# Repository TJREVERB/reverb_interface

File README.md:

# TJREVERB Interface Boards
Interface board rework, moved from Eagle to Kicad

The board provides power connections from the EPS and data connections from the flight computer to various components.

APRS and Iridium (through a MAX3232) are connected to UART, and can be selected between hardware UART and software/converter UART using jumpers. software/converter UART uses a converter as the primary UART device, with an option for software bit banging using RPi GPIO as a backup.

There are three branches: USB to UART, SPI to UART (DEPRECATED IN v1.4), and Multicore

The first is similar to the original design, and uses a USB to UART converter. 

The second uses an SPI to UART converter so that we can send data through the main Pi header instead of pogo pins or USB pads. DEPRECATED DUE TO DIFFICULTY IN SOFTWARE IMPLEMENTATION

The third uses an external AVR microcontroller as a secondary core, to be used for IO operations, specifically as an SPI/I2C to UART converter and an I2C buffer for sending delayed commands to the EPS (e.g. sending bus reset after a delay to give the pi enough time to exit script)

All branches include connections to bitbang uart instead of using the converter.

## Versions
v1.0 initial

v1.1 routing improvements

v1.2 fabricated first, received 10/24/21

v1.3 adds major corrections for circuitry

v1.4 introduces the new multicore branch

v1.5 replaces LSM9DS1 IMU with BNO055

v1.6 adds RTC and battery

v2.0 CAD compatibility check, fabbed as v2 on 11/28/21

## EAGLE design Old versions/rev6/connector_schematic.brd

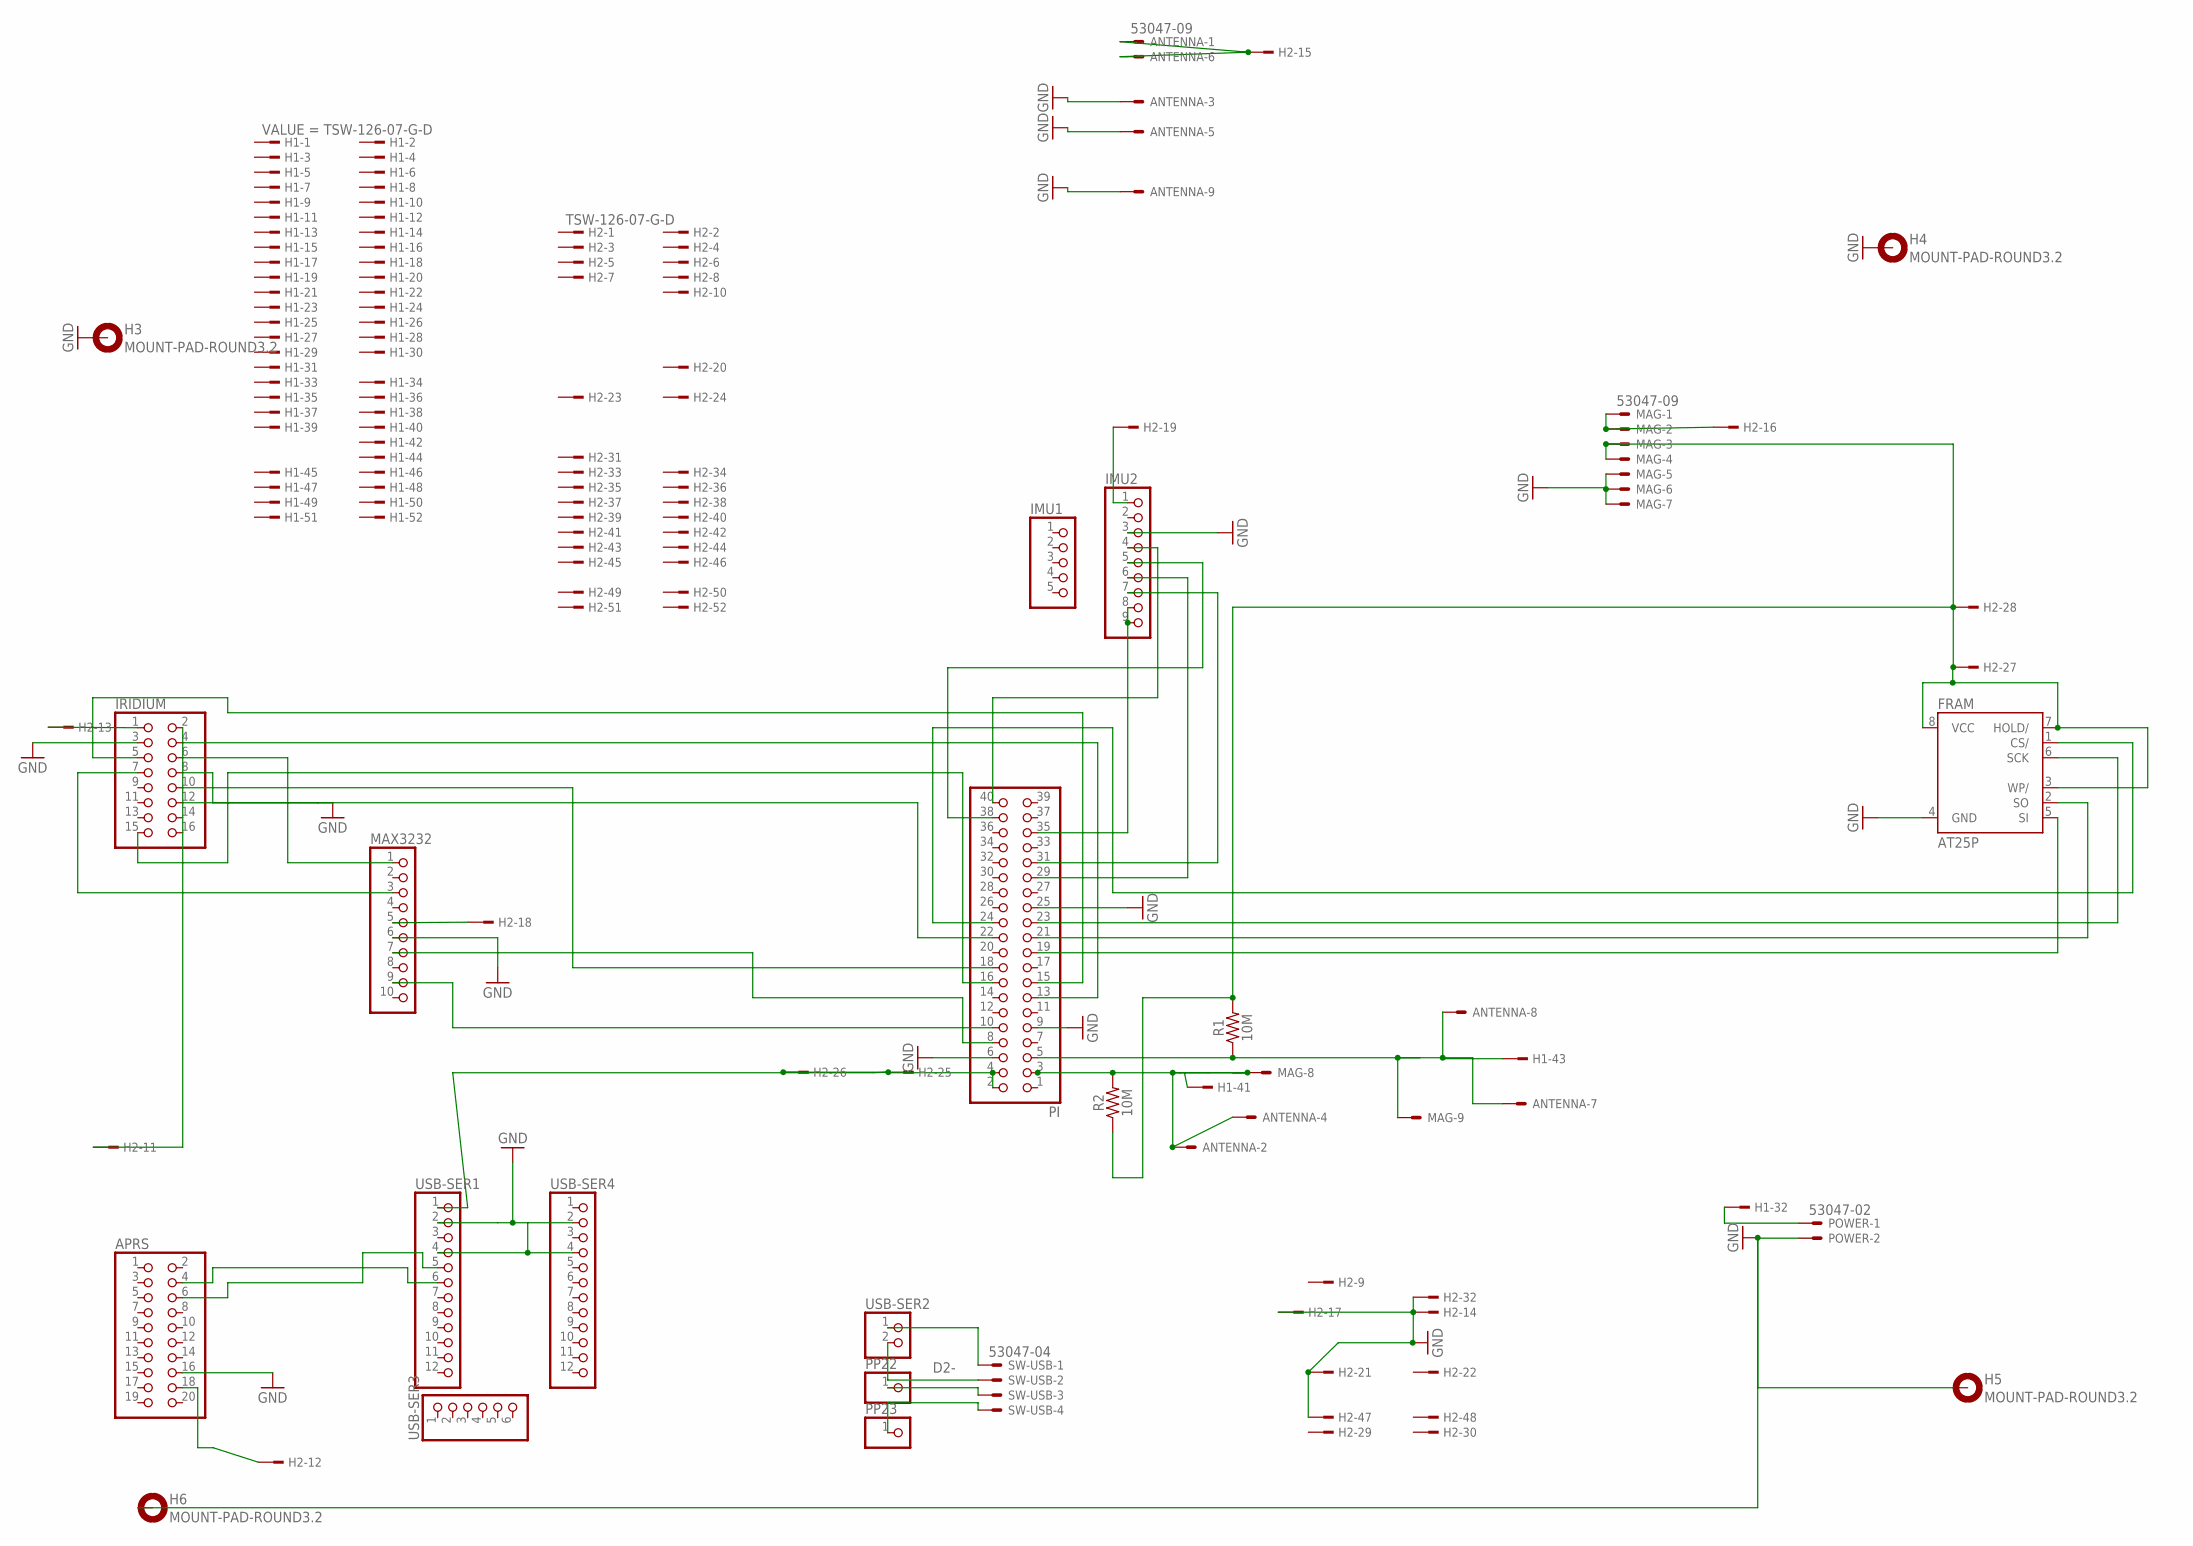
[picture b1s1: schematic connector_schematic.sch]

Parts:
ANTENNA: 53047-09
APRS: PINHD-2X10; 2X10
FRAM: AT25P; DIL08
H1, H2: TSW-126-07-G-D; TSW-126-XX-G-D
H3, H4, H5, H6: MOUNT-PAD-ROUND3.2; 3,2-PAD
IMU1: PINHD-1X5; 1X05
IMU2: PINHD-1X9; 1X09
IRIDIUM: PINHD-2X8; 2X08
MAG: 53047-09
MAX3232: PINHD-1X10; 1X10
PI: PINHD-2X20; 2X20
POWER: 53047-02
PP22, PP23: PINHD-1X1; 1X01
R1, R2: 10M; AXIAL-0.3
SW-USB: 53047-04
USB-SER1, USB-SER4: PINHD-1X12; 1X12
USB-SER2: PINHD-1X2; 1X02
USB-SER3: PINHD-1X6; 1X06

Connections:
3V3: FRAM.3 (WP/), FRAM.7 (HOLD/), FRAM.8 (VCC), H2.27, H2.28, MAG.3, MAG.4, R1.P$2 (2), R2.P$1 (1)
5V: H2.25, H2.26, PI.2, PI.4, USB-SER1.1
D2+: SW-USB.1, USB-SER2.1
D2-: SW-USB.2, USB-SER2.2
D+: PP22.1, SW-USB.3
D-: PP23.1, SW-USB.4
GND: ANTENNA.3, ANTENNA.5, ANTENNA.9, APRS.16, FRAM.4 (GND), H2.14, H2.17, H2.21, H2.32, H2.47, H3.B3,2, H4.B3,2, H5.B3,2, H6.B3,2, IMU2.3, IRIDIUM.3, IRIDIUM.8, MAG.5, MAG.6, MAG.7, MAX3232.6, PI.6, PI.9, PI.25, POWER.2, USB-SER1.2, USB-SER1.4, USB-SER4.2, USB-SER4.4
unnamed: APRS.18, H2.12
unnamed: IMU2.5, PI.38
unnamed: APRS.6, USB-SER1.5
unnamed: H2.19, IMU2.1
unnamed: ANTENNA.1, ANTENNA.6, H2.15
unnamed: H2.13, IRIDIUM.1
unnamed: IRIDIUM.4, PI.13
unnamed: IRIDIUM.5, PI.15
unnamed: IRIDIUM.15, PI.16
unnamed: IRIDIUM.10, PI.18
unnamed: MAX3232.7, PI.8
unnamed: H1.32, POWER.1
unnamed: APRS.4, USB-SER1.6
unnamed: IRIDIUM.12, PI.22
unnamed: H2.11, IRIDIUM.2
unnamed: FRAM.5 (SI), PI.19
unnamed: FRAM.6 (SCK), PI.23
unnamed: FRAM.1 (CS/), PI.24
unnamed: FRAM.2 (SO), PI.21
unnamed: MAX3232.9, PI.10
unnamed: IRIDIUM.6, MAX3232.1
unnamed: IRIDIUM.7, MAX3232.3
unnamed: IMU2.4, PI.40
unnamed: IMU2.6, PI.29
unnamed: IMU2.7, PI.31
unnamed: IMU2.8, IMU2.9, PI.35
unnamed: H2.16, MAG.1, MAG.2
unnamed: H2.18, MAX3232.5
SCL: ANTENNA.7, ANTENNA.8, H1.43, MAG.9, PI.5, R1.P$1 (1)
SDA: ANTENNA.2, ANTENNA.4, H1.41, MAG.8, PI.3, R2.P$2 (2)

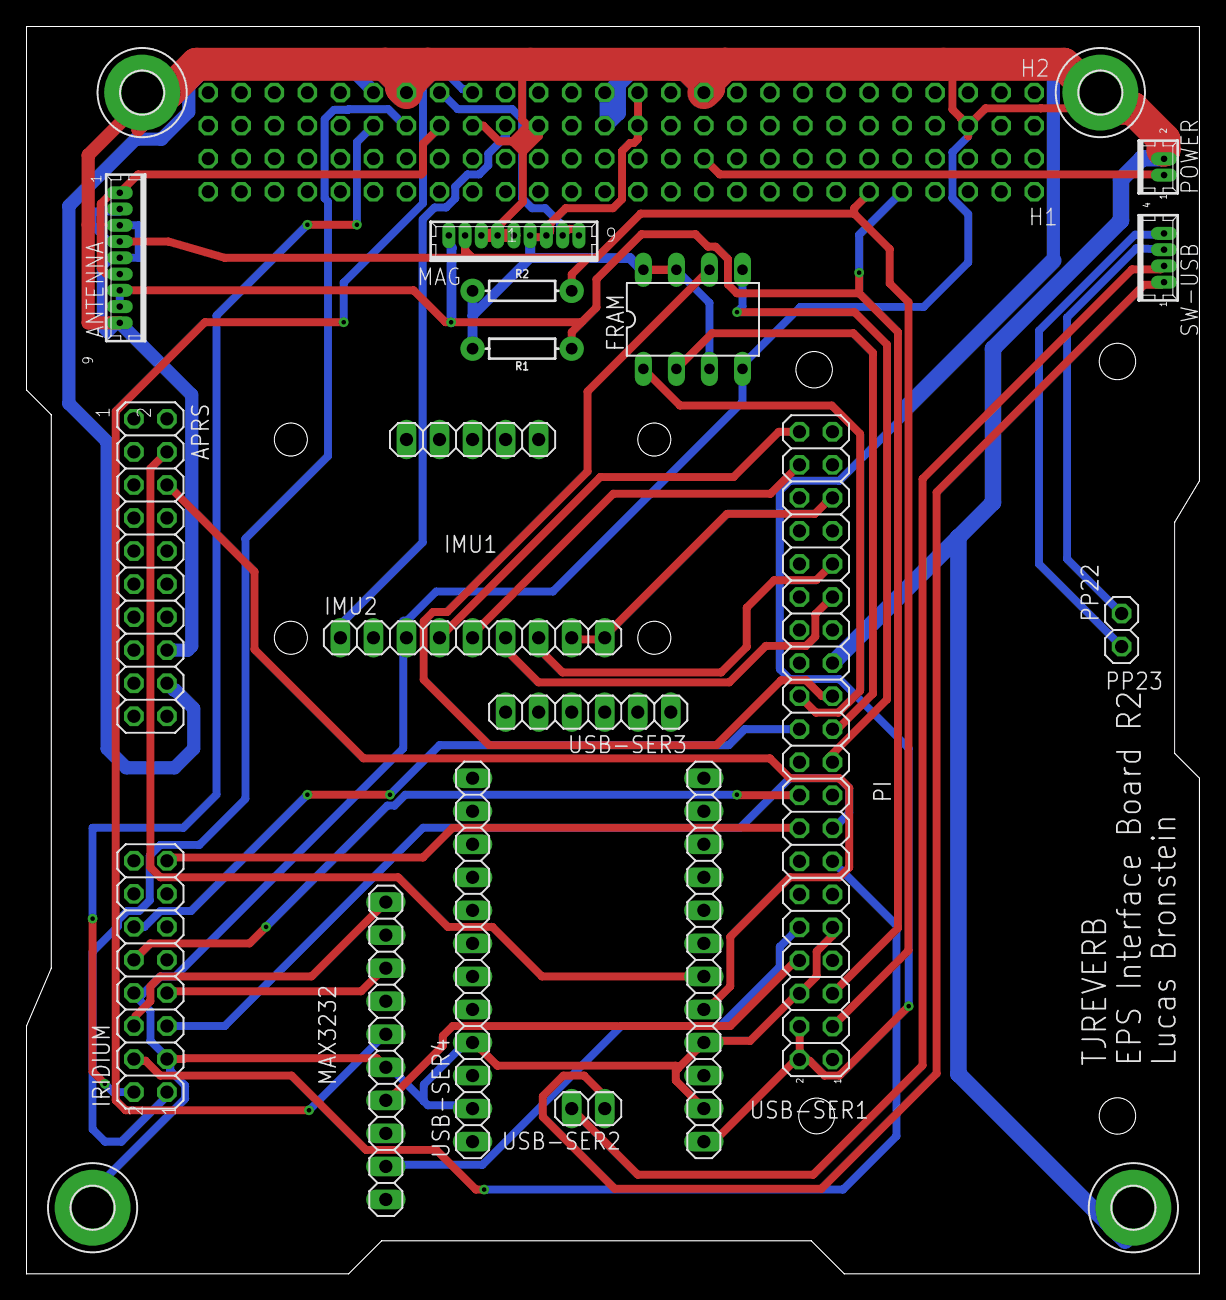
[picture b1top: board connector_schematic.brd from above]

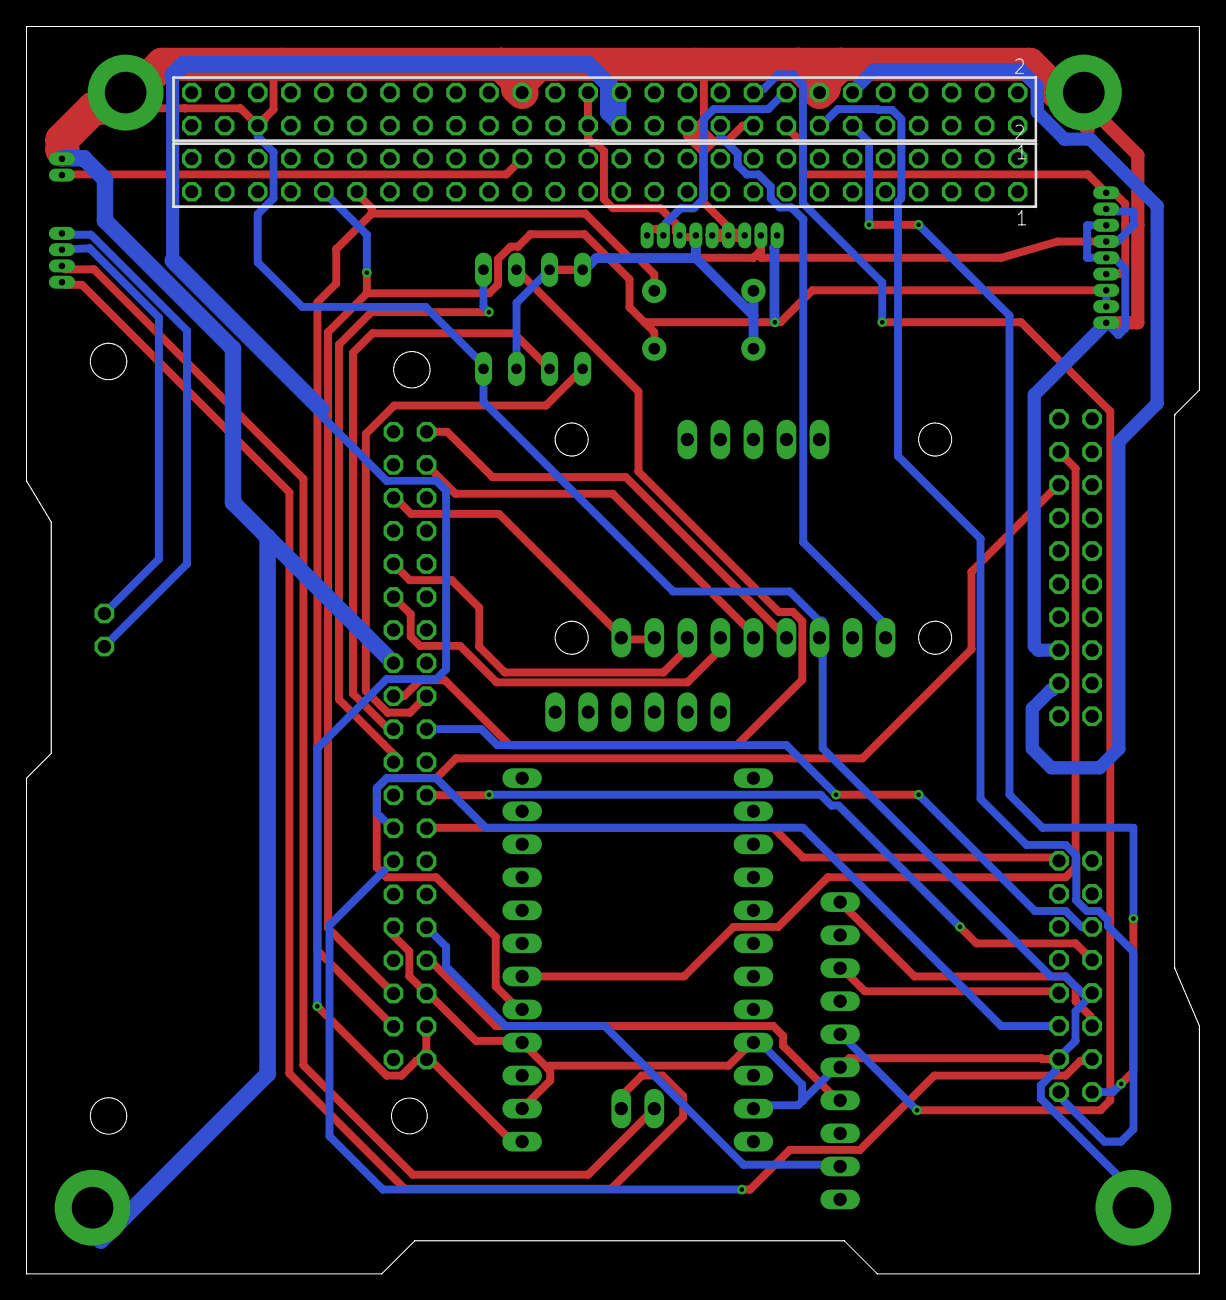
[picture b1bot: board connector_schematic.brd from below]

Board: 2 copper layers, 90.2 x 95.9 mm, 25 parts (2 on the bottom side), 37 nets.

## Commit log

2021-10-03 Establish file structure, add archived versions
2021-10-03 Schematic work: added EPS and Pi Headers
2021-10-03 mounting holes and ground connections
2021-10-05 work
2021-10-06 add capacitors to max3232
2021-10-06 wiring work
2021-10-07 footprint associations
2021-10-07 create board, finish footprint association
2021-10-07 copy old board layout positions
2021-10-07 silkscreen labels
2021-10-07 do stuff
2021-10-09 bunch of work
2021-10-09 add solder jumpers
2021-10-09 routing work
2021-10-10 finsihing up routing
2021-10-10 finishing up for real now
2021-10-10 create spi to uart branch
2021-10-10 fix a via
2021-10-10 Add LDO to convert 5V USB logic to 3V3 UART
2021-10-10 fix silkscreen, add another ground via
2021-10-10 spi edits
2021-10-10 SPI Branch routing
2021-10-10 update silkscreen
2021-10-10 Add RTS and CTS connections to layout
2021-10-11 Add LEDs for all used PDMs
2021-10-13 visual cleanup
2021-10-13 Remove LDO
2021-10-13 Add note regarding usb programming
2021-10-14 Routing EMI considerations
2021-10-15 EMI and SI minmaxing, round 2
2021-10-15 Combined files for smt stencil
    *NOT PANELIZED*
2021-10-15 Replace max3232 footprint, update stencil
2021-10-15 update silkscreen again
2021-10-24 Remove incorrect uart flow control connections, pull CTS low. Improve silkscreen placement
    Issue #3 and Issue #5
2021-10-24 Improve usb branch silkscreen, push v1.3
    #5 Will need to verify required clearance for connector housing later.
2021-10-24 Add bitbang uart connections
    gpio 23 and 24, #2
2021-10-24 Correct RPi symbol GPIO numbers
2021-10-27 Add level shifters, updated sch revision numbers consistent with pcb
2021-10-28 add level shifter to routing
    #1
2021-11-03 Fix USB header placement
2021-11-03 add switch led silkscreen labels
2021-11-04 Deprecate SPI branch, push v1.4, add new "multicore" branch, remove combined board files
2021-11-04 Update documentation
2021-11-05 tie OE high
2021-11-06 Add decoupling
2021-11-08 fix imu implementation, add bno055 compatibility
2021-11-08 fix imu implementation on multicore branch
2021-11-08 add attiny firmware first version
2021-11-09 I have no idea what Im doing with this firmware
2021-11-11 add protocol info
2021-11-11 intermediate commit
2021-11-12 finish bno055 mod, push v1.5
2021-11-12 gerber export
2021-11-15 RI line
2021-11-15 route, edit i2c description
2021-11-16 implement rtc on a pdm
2021-11-16 embed the rtc
2021-11-17 fix some compile time errors
2021-11-17 add footprints, may need to use smaller battery
2021-11-18 3d model updates
2021-11-18 Remove RI line
2021-11-19 add usb switch
2021-11-19 finish routing rtc
2021-11-21 add microusb breakout board
2021-11-22 Move some parts around, remove UART LEDs, .step export, push v1.6
2021-11-26 start on adding i2c-0 option
2021-11-26 add i2c0 option
2021-11-26 tidy up the schematic, for usb branch
2021-11-26 finish tidying up schematics
2021-11-26 new gerber exports
2021-11-28 stack conflict checking
2021-11-28 push v2.0
2021-11-28 remove usb pogo
2021-11-28 remove zips
2021-11-30 move gerbers, add combined branches gerber again
2021-12-04 replace SPI slave with I2C slave

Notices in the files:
parts and their libraries:
SparkFun-Resistors: Licensing: Creative Commons ShareAlike 4.0 International - https://creativecommons.org/licenses/by-sa/4.0
